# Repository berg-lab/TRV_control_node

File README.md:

# TRV_control_node
First generation radiator control based on Raspberry Pi Zero W

Refer to Paper: [Development and evaluation of an automatic steam radiator control system for retrofitting legacy heating systems in existing buildings](https://www.sciencedirect.com/science/article/abs/pii/S0378778821006289)

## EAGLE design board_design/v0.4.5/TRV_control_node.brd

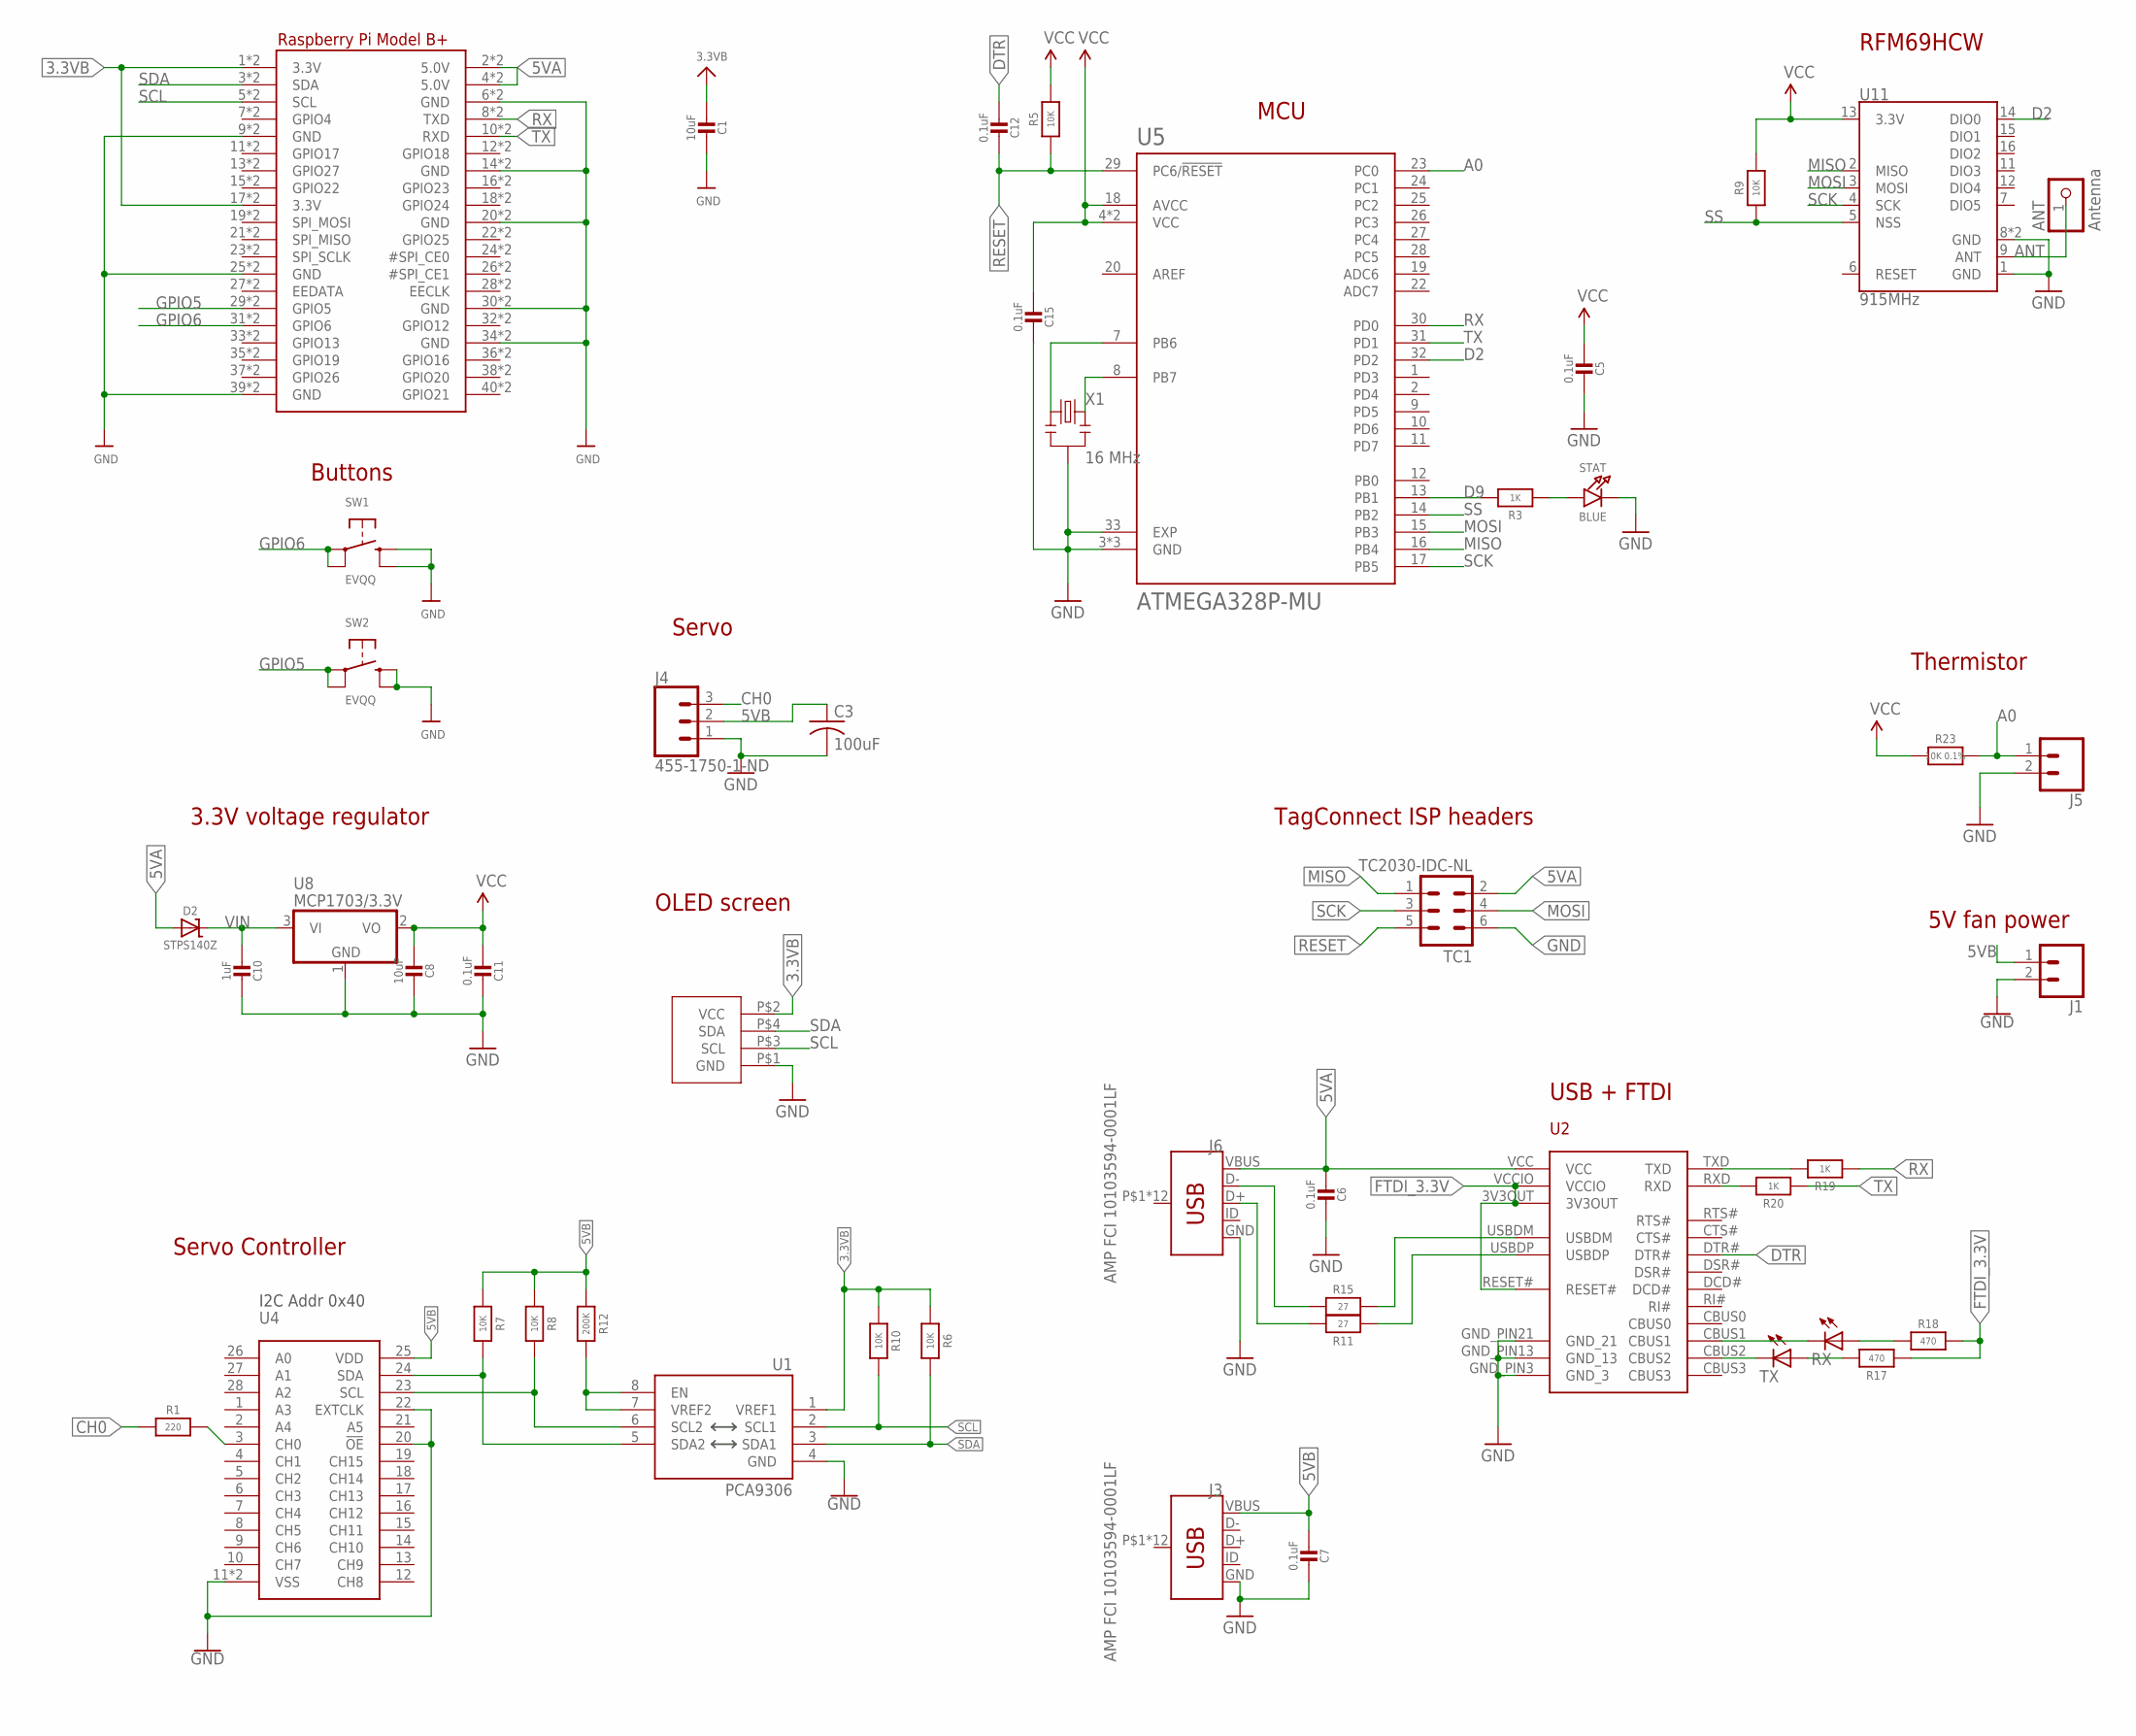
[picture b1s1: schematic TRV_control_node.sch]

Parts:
ANT: Antenna; 1X01-CLEANBIG; MPN Helical antenna
C1, C8: 10uF; MICROBUILDER__0402MP; MPN GRM155R71C104KA88J
C3: 100uF; C1210
C5, C6, C7, C11, C12, C15: 0.1uF; MICROBUILDER__0402MP; MPN GRM155R71C104KA88J
C10: 1uF; MICROBUILDER__0402MP; MPN GRM155R71C104KA88J
D2: STPS140Z; MICROBUILDER_SOD-123; MPN SD103AW-13-F
J1, J5: CONN_02; 1X02
J3, J6: AMP FCI 10103594-0001LF; USB-MICROB-PTH
J4: 455-1750-1-ND; 1X03
R1: 220; MICROBUILDER__0402MP; MPN RC0402JR-071KL
R3: 1K; MICROBUILDER__0402MP; MPN RC0402JR-0710KL
R5, R9: 10K; MICROBUILDER__0402MP; MPN RC0402JR-0710KL
R6, R7, R8, R10: 10K; MICROBUILDER__0402MP; MPN RC0402JR-071KL
R11, R15: 27; MICROBUILDER__0402MP; MPN RC0402JR-0727RL
R12: 200K; MICROBUILDER__0402MP; MPN RC0402JR-071KL
R17, R18: 470; MICROBUILDER__0402MP; MPN RC0402JR-07470RL
R19, R20: 1K; MICROBUILDER__0402MP; MPN RC0402JR-071KL
R23: 10K 0.1%; MICROBUILDER__0402MP; MPN RC0402JR-0727RL
RPI1: RASPBERRYPI_BPLUS_BONNET_THMSMT; PI_BONNET_THMSMT
RX: LEDCHIPLED_0805; CHIPLED_0805; MPN LG R971-KN-1
STAT: BLUE; CHIPLED_0805_NOOUTLINE
SW1, SW2: EVQQ; EVQ-Q2_SMALLER
TC1: TC2030-IDC-NL
TX: LEDCHIPLED_0805; CHIPLED_0805; MPN LG R971-KN-1
U1: PCA9306; PSOP-8
U2: FT231XQ-R; FTDI_FT231XQ-R_PACKAGE; MPN FT231XQ-R
U4: PCA9685HVQFN28; HVQFN28_SOT788-1
U5: ATMEGA328P-MU; QFN50P500X500X100-33N; MPN ATMEGA328P-MU
U8: MCP1703/3.3V; SOT23; MPN MCP1703T-3302E/CB
U11: 915MHz; RFM69HCW-XXXS2; MPN RFM69HCW
U$1: OLED_091_SSD1306; OLED_128X32_0.91
X1: 16 MHz; RESONATOR-SMD; MPN CSTCE16M0V53-R0

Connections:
3.3VB: C1.2, R6.1, R10.1, RPI1.1 (3.3V), RPI1.17 (3.3V), RPI1.S1 (3.3V), RPI1.S17 (3.3V), U1.1 (VREF1), U$1.P$2 (VCC)
5VA: C6.2, D2.A, J6.VBUS, RPI1.2 (5.0V), RPI1.4 (5.0V), RPI1.S2 (5.0V), RPI1.S4 (5.0V), TC1.2, U2.VCC
5VB: C3.1, C7.2, J1.1, J3.VBUS, J4.2, R7.1, R8.1, R12.1, U4.25 (VDD)
A0: J5.1, R23.2, U5.23 (PC0)
ANT: ANT.1, U11.9 (ANT)
CH0: J4.3, R1.1
D2: U5.32 (PD2), U11.14 (DIO0)
D9: R3.2, U5.13 (PB1)
DTR: C12.2, U2.DTR#
FTDI_3.3V: R17.1, R18.2, U2.3V3OUT, U2.RESET#, U2.VCCIO
GND: C1.1, C3.2, C5.1, C6.1, C7.1, C8.1, C10.1, C11.1, C15.1, J1.2, J3.GND, J4.1, J5.2, J6.GND, RPI1.6 (GND), RPI1.9 (GND), RPI1.14 (GND), RPI1.20 (GND), RPI1.25 (GND), RPI1.30 (GND), RPI1.34 (GND), RPI1.39 (GND), RPI1.S6 (GND), RPI1.S9 (GND), RPI1.S14 (GND), RPI1.S20 (GND), RPI1.S25 (GND), RPI1.S30 (GND), RPI1.S34 (GND), RPI1.S39 (GND), STAT.C, SW1.B (S), SW1.B' (S1), SW2.B (S), SW2.B' (S1), TC1.6, U1.4 (GND), U2.GND_PIN3 (GND_3), U2.GND_PIN13 (GND_13), U2.GND_PIN21 (GND_21), U4.11 (VSS), U4.20 (!OE), U4.22 (EXTCLK), U4.TH (VSS), U5.3 (GND), U5.5 (GND), U5.21 (GND), U5.33 (EXP), U8.1 (GND), U11.1 (GND), U11.8 (GND), U11.10 (GND), U$1.P$1 (GND), X1.2
GPIO5: RPI1.29 (GPIO5), RPI1.S29 (GPIO5), SW2.A, SW2.A' (P1)
GPIO6: RPI1.31 (GPIO6), RPI1.S31 (GPIO6), SW1.A, SW1.A' (P1)
MISO: TC1.1, U5.16 (PB4), U11.2 (MISO)
MOSI: TC1.4, U5.15 (PB3), U11.3 (MOSI)
unnamed: R12.2, U1.7 (VREF2), U1.8 (EN)
unnamed: R20.2, U2.RXD
unnamed: R19.2, U2.TXD
unnamed: U5.8 (PB7), X1.3
unnamed: U5.7 (PB6), X1.1
unnamed: R8.2, U1.6 (SCL2), U4.23 (SCL)
unnamed: R7.2, U1.5 (SDA2), U4.24 (SDA)
unnamed: R3.1, STAT.A
unnamed: R1.2, U4.3 (CH0)
unnamed: RX.C, U2.CBUS1
unnamed: TX.C, U2.CBUS2
unnamed: R15.2, U2.USBDM
unnamed: R11.1, U2.USBDP
unnamed: R18.1, RX.A
unnamed: R17.2, TX.A
unnamed: J6.D-, R15.1
unnamed: J6.D+, R11.2
RESET: C12.1, R5.1, TC1.5, U5.29 (PC6/!RESET)
RX: R19.1, RPI1.8 (TXD), RPI1.S8 (TXD), U5.30 (PD0)
SCK: TC1.3, U5.17 (PB5), U11.4 (SCK)
SCL: R10.2, RPI1.5 (SCL), RPI1.S5 (SCL), U1.2 (SCL1), U$1.P$3 (SCL)
SDA: R6.2, RPI1.3 (SDA), RPI1.S3 (SDA), U1.3 (SDA1), U$1.P$4 (SDA)
SS: R9.1, U5.14 (PB2), U11.5 (NSS)
TX: R20.1, RPI1.10 (RXD), RPI1.S10 (RXD), U5.31 (PD1)
VCC: C5.2, C8.2, C11.2, C15.2, R5.2, R9.2, R23.1, U5.4 (VCC), U5.6 (VCC), U5.18 (AVCC), U8.2 (VO), U11.13 (3.3V)
VIN: C10.2, D2.C, U8.3 (VI)

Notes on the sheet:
MCU
USB + FTDI
RFM69HCW
TagConnect ISP headers
3.3V voltage regulator
I2C Addr 0x40
Servo
Servo Controller
OLED screen
Buttons
Thermistor
5V fan power

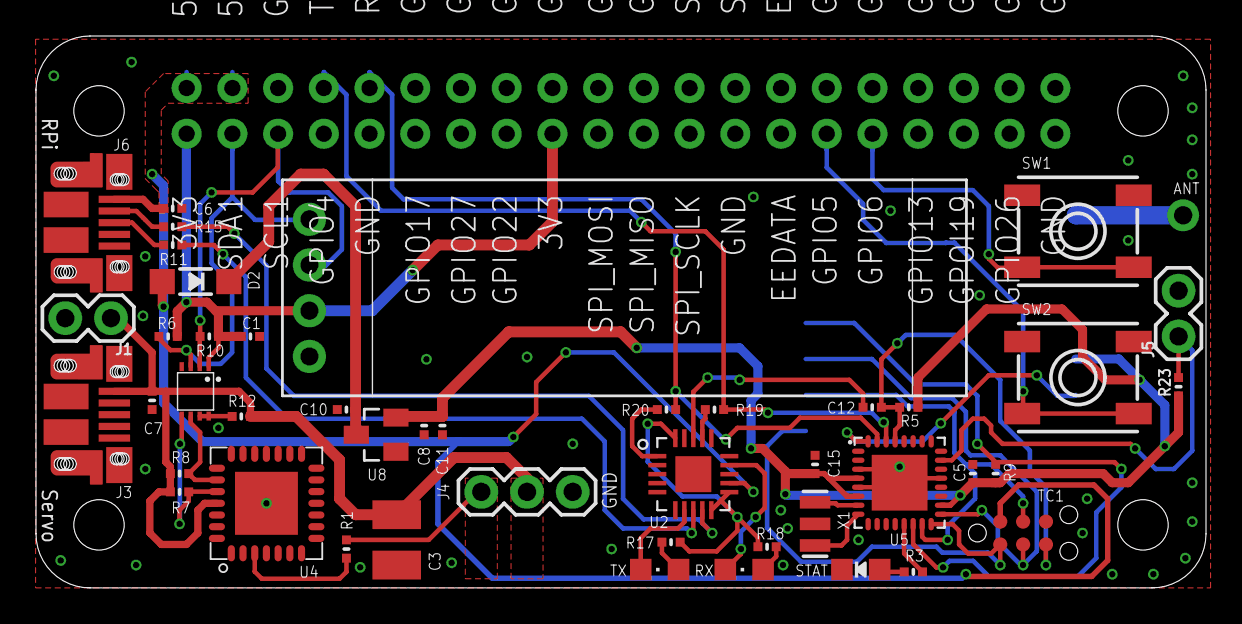
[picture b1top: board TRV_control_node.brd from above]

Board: 2 copper layers, 65.0 x 30.7 mm, 48 parts (1 on the bottom side), 41 nets.

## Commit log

2018-06-01 schematic changes
2018-06-04 Arranged components on brd
2018-06-05 Completed routing
2018-06-05 Adjustments
    - Removed second OLED screen pins
    - Moved USB ports slightly away from each other
    - Silkscreen adjustments
2018-06-06 USB ports adjustment
    - Moved USB ports a bit further away
    - Some trace adjustments
    - ERC and DRC
    - Some silkscreen adjustments
2018-06-07 v0.4.1 - update
    - Changed TSSOP28 package for PCA9685 to HVQFN28
    - Moved 3.3V vreg from under the OLED to right below it
    - Silkscreen adjustments
    - Trace adjustments
    - Exported gerbers for v0.4.0 and v0.4.1
    - ERC & DRC check
2018-06-07 vreg adjustment
    Moved the Vreg and its caps a bit away from the 3 pin servo header
2018-06-07 added updated gerbers
2018-07-18 v0.4.2 - bug fixes
    - Connected SDA and SCL for servo control (had incorrect net names in schematic)
    - Fixed servo header pins (sig and power were flipped)
    - Silkscreen adjustment
    - Maintained same tcream (components weren't moved) - can reuse stencil for v0.4.1
    - DRC
2018-07-19 small update
    - Moved via a bit
    - Silkscreen adjustment
    - Removed some wire stubs
2018-08-06 Added firmware
2018-08-21 v0.4.3 - small update
    - Moved 3 pin servo header back to allow right-angled male pins or just wires to be directly soldered there
    - Moved ANT via to the corner of board
    - Moved buttons a bit lower
    - Added header for analog input (thermistor with 10K resistor pad)
    - Silkscreen and trace adjustments to accomodate design update
    - ERC/DRC
2018-08-21 silkscreen update + added gerbers
2018-09-04 v0.4.2b & v0.4.3 - proper versioning & update
    - Renamed v0.4.3 to v0.4.2b -- this design is not used as some parts are physically "moved" on the board.
    - v0.4.3 - this design now incorporates the following:
    - thermistor header pins for extra temperature monitoring if needed
    - Relocation of antenna hole away from buttons
    - Added SMD pads for servo
    - silkscreen update
2018-09-04 Updated gerber files
2018-09-06 Added gerbers for v0.4.3
2018-10-15 V0.4.4 - added fan power pins breakout
    - moved some traces
    - adjusted vias
    - silkscreen update
    - ERC/DRC
2018-10-15 Added v0.4.4 gerbers
2018-10-15 updated antenna trace
    moved antenna pin header to the side to allow easy soldering
2018-10-30 ID, ATC, serial
    - Updated network and gateway IDs - now switches network ID on the fly
    - Default send with retry
    - Radio ATC
    - Now reads entire string instead of just one char - a bit slower but necessary for sending full packets to gateway
    - Removed RSSI from room node (gateway should append it either way)
2018-11-21 v0.5.1 firmware update
    - Added fadeLED to indicate boot/reset
    - Serial available now checks for "SET" to read setpoint and manual override
    - updated ACK for local nodes
    - added code to read thermistor every ~30 sec and send data
    - adjusted memset and other minor code fixes
    - added code for bare sender: only checks serial for "SET" and sends data
2019-05-02 Added RPi firmware
    also reorganized the directory structure
2019-05-02 moved board design files
2019-06-12 firmware updated for v0.5.2
2019-10-17 v0.4.5
    - Added silkscreen at the back of the board for Node IDs
    - Changed soldermask limit to 14mil to cover vias for a cleaner look
    - ERC/DRC
    - functionally same board as v0.4.4 - no other trace or component changes
2019-10-17 Added gerbers for v0.4.5
2019-10-17 updated gerbers to exclude tNames layer
2019-10-30 v0.5.2 - RPi firmware
    - Added diagnostics in readGPIO firmware that checks and running scripts, displays IP address, disk space and current data time. Access diagnostic by pressing and holding both buttons for 3 seconds. 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
2019-12-13 updated HAT firmware - v0.53
    - fixed split of setpoint and manual override
    - also added PWM values to be sent
    Explanation of changes: now allows setpoint values larger than 1 digit and expects the format: "<71,1, 243>" where '<' and '>' are start and end markers and 71 is setpoint (could also be 5, for examp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
    - PWM value takes the key 'w' in the dictionary
2019-12-18 Added v5.3 scripts
    small change in firmware of Pi and HAT
2019-12-18 v6.0 - major update
    - everything now comes from a config file from server.
    - all scripts updated to check config file and respond in real time
    - added new control strategy - pid control for temp and pid control with motion detection
    - many many minor bug fixes and exception handling
    - screen rotation on the fly
    - everything controlled by GUI - can even set servo type and control strategy as needed
2019-12-18 v6.1 - update
    - now logging PID values as well
    - other minor bug fixes
    - forgot to mention in previous update - version number now changed to v6.1 instead of v0.6.1. Ready for prime time!
2019-12-18 Update read_GPIO.py
    - minor bug fix to account for different control strategies
2019-12-18 Update read_GPIO.py
    - bug fix: save proper setpoint at boot so the temp setpoint in file matches the control strategy selected
2019-12-18 Update read_GPIO.py
    - fixed screen rotation and screen not loading up on boot
2019-12-20 Update read_serial.py
    - added try except to ignore node ID dataline coming from nodes
2019-12-20 v6.0 HAT firmware
    - same as v053, except serial print for node ID is now removed
2019-12-22 updated config.py
    - fixed getting node info from slug via acf
    - delete config file on boot and create new file
2019-12-23 Update firmware_v6.0.ino
    - fixed node id
    - added handling of node id by radio packet and appending it (from sensor data)
    - fixed handling of radiator surface temperature datapacket
    - automatic changing of node ID in the RFM69 library to assign different node ID for surface temp node
    - removed old code for setpoint id
2019-12-25 minor updates
    - fixed some time delays and some handling of things in various scripts
2019-12-25 Update rc.local
    changed order of scripts
2019-12-28 Update read_GPIO.py
    updatedsave setpoint command - now there is a separate save for start (where manual override is initially 0), and save is removed every 30 seconds. Setpoint is now only updated when button is pressed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
2019-12-29 config update
    - added default config file to load incase there is no internet connection on boot
    - added better exception handling for empty config file
    - removed deleting old config files on script start
2020-01-03 Update config.py
    - added function to check running scripts and return binary string
    - updated put function to accomodate sending different json packets to server identified by argument. Now network info and node status can be sent separately when needed
    - send node status (last updated time and running scripts) every hour
    - other minor code edits
2020-01-05 Update config.py
    - update network and status on server on script boot for faster debug
    - added a time delay after put is sent
    - put flag checks for both network and status scripts to be successful before being set
2020-01-29 check internet connection before attempting to get or put
    - also update config interval to 30 seconds instead of 10.
2020-01-29 v6.1 - firmware update
    - reorg code
    - change default freq (905MHz) and encryption key
    - changed some functions and delays to be more optimized
    - cleaned up code and made it neater
2020-02-04 update config and added new wpa
    - added extracting first field from hostname -I command so only IPv4 address is returned
    - added new wpa_supplicant.conf file for PEAP networks. Run upgrade script to change wpa version to stretch (if buster is being used)
2020-02-08 added old config again
2020-02-11 v6.2 update
    - datalogger function updated to initialize temp motion data file with no motion. This helps the checkmotion script to run on boot
    - config file updated to push proper IPv4 address and retry when no address available
    - config file also handles empty JSON response better so it doesn't crash the script entirely
    - added proper reboot flag to config file so node can be rebooted from server when needed
    - IP address and status now updated every hour
    - read GPIO function updated to display proper IPv4 address only (also version update on screen)
2020-02-11 don't delete temp data files
    - keep old files so scripts can pull data from there (resume where they left off before reboot)
    - this is a test - might change it back
2020-02-12 Update pid_temp.py
    bug fix
2020-02-13 fixed variable class bug
    - made pid temp offest a global variable, so it actually takes the values from server
2020-02-13 feature update - dynamic setpoints + PID
    - fixed PID tunings
    - read_GPIO now gets the upper and lower setpoint limits from server
    - same with temp setpoints
    - set_PWM now gets step size from server - can be dynamically adjusted
2020-02-13 bug fixes
    - temp offset is now float
    - moved temp upper and lower limits into if else blocks
2020-02-14 bug fix
    - type cast to int
2020-02-14 bug fix 2
    - type cast to int
2020-02-17 v7.0 - major update
    - This update changes a lot of the functionality of the nodes - incompatible with previous versions
    - Reboot and override flag iare now locally set in file as well as pushed to server to prevent bootloop and override loop
    - Added check motion "value", which allows either a custom setpoint value to be set after motion is detected, or the previously set value. Value retrived from server
    - CPU core temp is now sent to server
    - PWM value is now sent to server in raw as well as percentage of valve closed
    - dictionary updated to add new PID components as well as changed w to PWM, and x to PID output
2020-02-17 updated default config files
2020-02-17 bug fix with type casting PWM percentage
    also added missing temp_data_dir
2020-02-17 changed int back to round
2020-02-17 bug fixes
    - send status every 10 mins, send network every hour
    - save setpoint bug fix - based on control strategy
2020-02-17 datalogger script fix
    - added PID components to sensorTypes
    - commented out initial control node temp file - just need to wait for new data to come through instead
2020-02-18 manual override discrepancy fix
    - added proper reading of manual override in all scripts
    - should fix bug with random failed setpoint writes to file
2020-02-18 Update config.py
    setpoint override type cast to string
2020-02-18 added temp files
2020-02-23 added operative temp
    - new script that calculates operative temp based on globe temp and air temp and saves to file
    - all necessary scripts upgraded to switch between operantive and air temp
    - rc.local also updated to start operative temp script
    - new entry in dictionary
    - readgpio running scripts now have operative temp as extra script
2020-02-23 bug fixes
    - added more default config values
    - changed rc.local from dos to unix format
2020-02-23 setpoint step size bug fix
    default values assigned; script checks if config file contains step size and won't crash even if it doesn't
2020-02-23 running scripts
    changedrunning scripts in config
    updated default rc.local file
2020-02-23 Update read_GPIO.py
    check screen rotation in config json
2020-02-23 Update read_GPIO.py
    adding try except so script doesn't fail
2020-02-23 Update read_GPIO.py
    - added more time at boot so config file has time to load
2020-02-23 Update rc.local
    change default rc.local operative temp
2020-02-24 dangerous bug fix
    BUILDING BURNING BECAUSE PID KEPT ALL VALVES OPEN!
    - bug was filename took 2 arguments in string format, but 3 provided. Fixed scripts now
2020-02-27 Update pid_temp.py
    - only change pwm value if it's significantly different from previous value. If they're same, don't apply. Hopefully this removes stress from servo and prevents it from constantly going to a position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
2020-03-01 added BOM

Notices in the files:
parts and their libraries:
SparkFun-Aesthetics: Licensing: Creative Commons ShareAlike 4.0 International - https://creativecommons.org/licenses/by-sa/4.0
